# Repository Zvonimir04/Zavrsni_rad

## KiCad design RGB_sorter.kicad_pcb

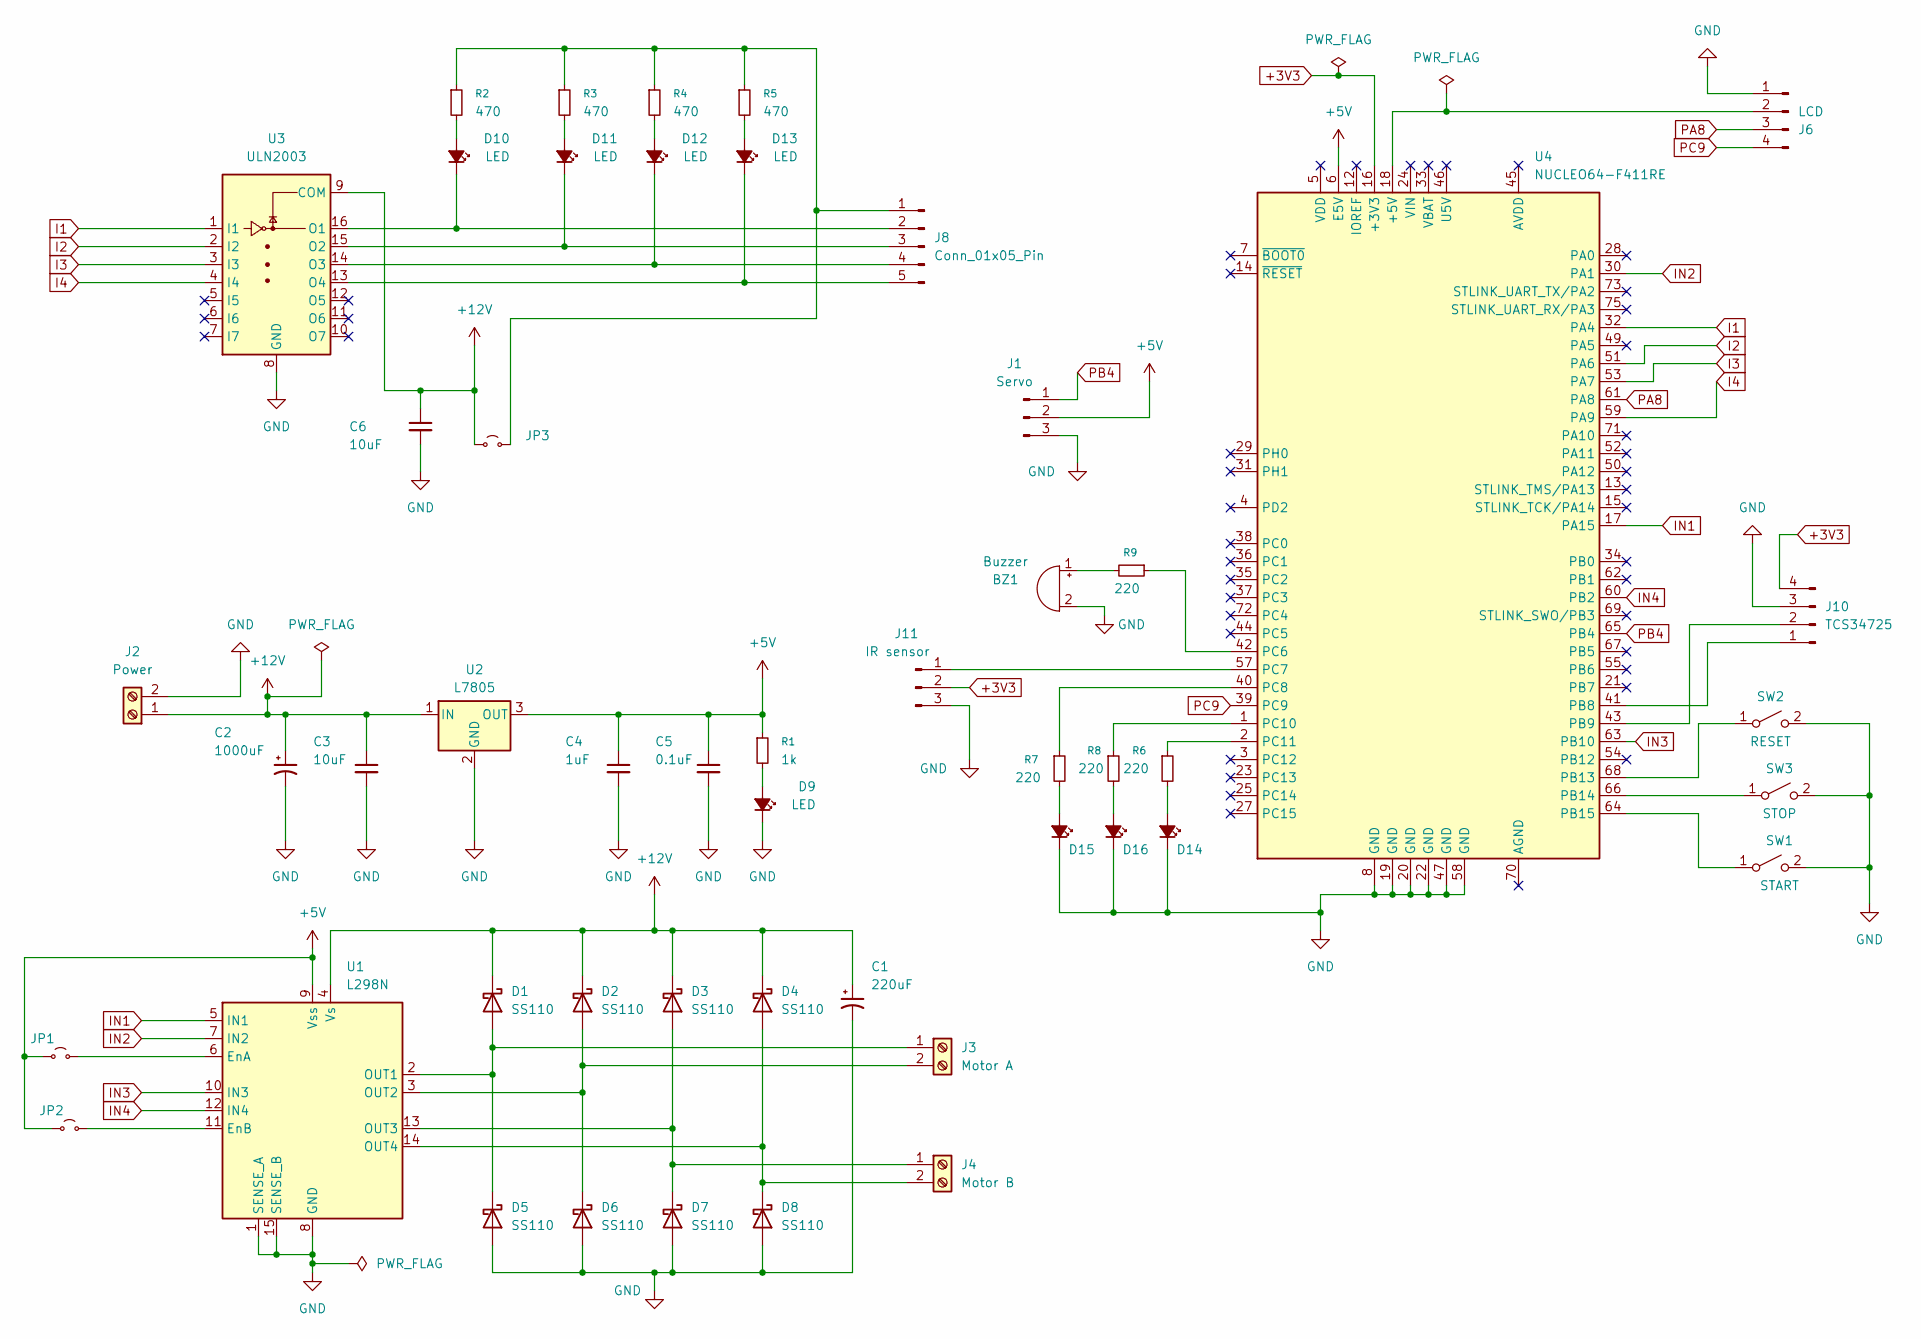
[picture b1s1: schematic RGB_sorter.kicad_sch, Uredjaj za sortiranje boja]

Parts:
BZ1: Buzzer; Buzzer_12x9.5RM7.6
C1: 220uF; CP_Elec_8x10.5
C2: 1000uF; CP_Elec_10x10.5
C3, C6: 10uF; C_1206_3216Metric
C4: 1uF; C_0805_2012Metric
C5: 0.1uF; C_0805_2012Metric
D1, D2, D3, D4, D5, D6, D7, D8: SS110; D_SMA
D9: LED; LED_0805_2012Metric
D10, D11, D12, D13: LED; LED_1206_3216Metric
D14: LED_Red; LED_D5.0mm
D15: LED_Green; LED_D5.0mm
D16: LED_Blue; LED_D5.0mm
J1: Servo; PinHeader_1x03_P2.54mm_Vertical
J2: Power; TerminalBlock_Phoenix_MKDS-1,5-2-5.08_1x02_P5.08mm_Horizont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
J3: Motor A; TerminalBlock_Phoenix_MKDS-1,5-2-5.08_1x02_P5.08mm_Horizont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
J4: Motor B; TerminalBlock_Phoenix_MKDS-1,5-2-5.08_1x02_P5.08mm_Horizont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
J6: LCD; PinHeader_1x04_P2.54mm_Vertical
J8: Conn_01x05_Pin; JST_XH_B5B-XH-A_1x05_P2.50mm_Vertical
J10: TCS34725; PinHeader_1x04_P2.54mm_Vertical
J11: IR sensor; PinHeader_1x03_P2.54mm_Vertical
JP1, JP2, JP3: PinHeader_1x02_P2.54mm_Vertical
R1: 1k; R_0805_2012Metric
R2, R3, R4, R5: 470; R_0805_2012Metric
R6, R7, R8, R9: 220; R_0805_2012Metric
SW1: START; SW_PUSH-12mm_Wuerth-430476085716
SW2: RESET; SW_PUSH-12mm_Wuerth-430476085716
SW3: STOP; SW_PUSH-12mm_Wuerth-430476085716
U1: L298N; L298n
U2: L7805; TO-252-2
U3: ULN2003; SOIC-16_3.9x9.9mm_P1.27mm
U4: NUCLEO64-F411RE; MODULE_NUCLEO-F446RE

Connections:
+3V3: J10.4, J11.2, U4.16 (+3V3)
+5V: C4.1, C5.1, J1.2, JP1.1 (A), JP2.1 (A), R1.1, U1.9 (Vss), U2.3 (OUT), U4.6 (E5V)
+12V: C1.1, C2.1, C3.1, C6.1, D1.1 (K), D2.1 (K), D3.1 (K), D4.1 (K), J2.1, JP3.1 (A), U1.4 (Vs), U2.1 (IN), U3.9 (COM)
GND: BZ1.2 (-), C1.2, C2.2, C3.2, C4.2, C5.2, C6.2, D5.2 (A), D6.2 (A), D7.2 (A), D8.2 (A), D9.1 (K), D14.1 (K), D15.1 (K), D16.1 (K), J1.3, J2.2, J6.1, J10.3, J11.3, SW1.2 (B), SW2.2 (B), SW3.2 (B), U1.1 (SENSE_A), U1.8 (GND), U1.15 (SENSE_B), U2.2 (GND), U3.8 (GND), U4.8 (GND), U4.19 (GND), U4.20 (GND), U4.22 (GND), U4.47 (GND), U4.58 (GND)
I1: U3.1 (I1), U4.32 (PA4)
I2: U3.2 (I2), U4.51 (PA6)
I3: U3.3 (I3), U4.53 (PA7)
I4: U3.4 (I4), U4.59 (PA9)
IN1: U1.5 (IN1), U4.17 (PA15)
IN2: U1.7 (IN2), U4.30 (PA1)
IN3: U1.10 (IN3), U4.63 (PB10)
IN4: U1.12 (IN4), U4.60 (PB2)
unnamed: BZ1.1 (+), R9.2
unnamed: D1.2 (A), D5.1 (K), J3.1, U1.2 (OUT1)
unnamed: D2.2 (A), D6.1 (K), J3.2, U1.3 (OUT2)
unnamed: D3.2 (A), D7.1 (K), J4.1, U1.13 (OUT3)
unnamed: D4.2 (A), D8.1 (K), J4.2, U1.14 (OUT4)
unnamed: D9.2 (A), R1.2
unnamed: D10.2 (A), R2.2
unnamed: D10.1 (K), J8.2, U3.16 (O1)
unnamed: D11.2 (A), R3.2
unnamed: D11.1 (K), J8.3, U3.15 (O2)
unnamed: D12.2 (A), R4.2
unnamed: D12.1 (K), J8.4, U3.14 (O3)
unnamed: D13.2 (A), R5.2
unnamed: D13.1 (K), J8.5, U3.13 (O4)
unnamed: D14.2 (A), R6.2
unnamed: D15.2 (A), R7.2
unnamed: D16.2 (A), R8.2
unnamed: J6.2, U4.18 (+5V)
unnamed: J8.1, JP3.2 (B), R2.1, R3.1, R4.1, R5.1
unnamed: J10.1, U4.41 (PB8)
unnamed: J10.2, U4.43 (PB9)
unnamed: J11.1, U4.57 (PC7)
unnamed: JP1.2 (B), U1.6 (EnA)
unnamed: JP2.2 (B), U1.11 (EnB)
unnamed: SW1.1 (A), U4.64 (PB15)
unnamed: SW2.1 (A), U4.68 (PB13)
unnamed: SW3.1 (A), U4.66 (PB14)
unnamed: R9.1, U4.42 (PC6)
unnamed: R7.1, U4.40 (PC8)
unnamed: R8.1, U4.1 (PC10)
unnamed: R6.1, U4.2 (PC11)
PA8: J6.3, U4.61 (PA8)
PB4: J1.1, U4.65 (PB4)
PC9: J6.4, U4.39 (PC9)

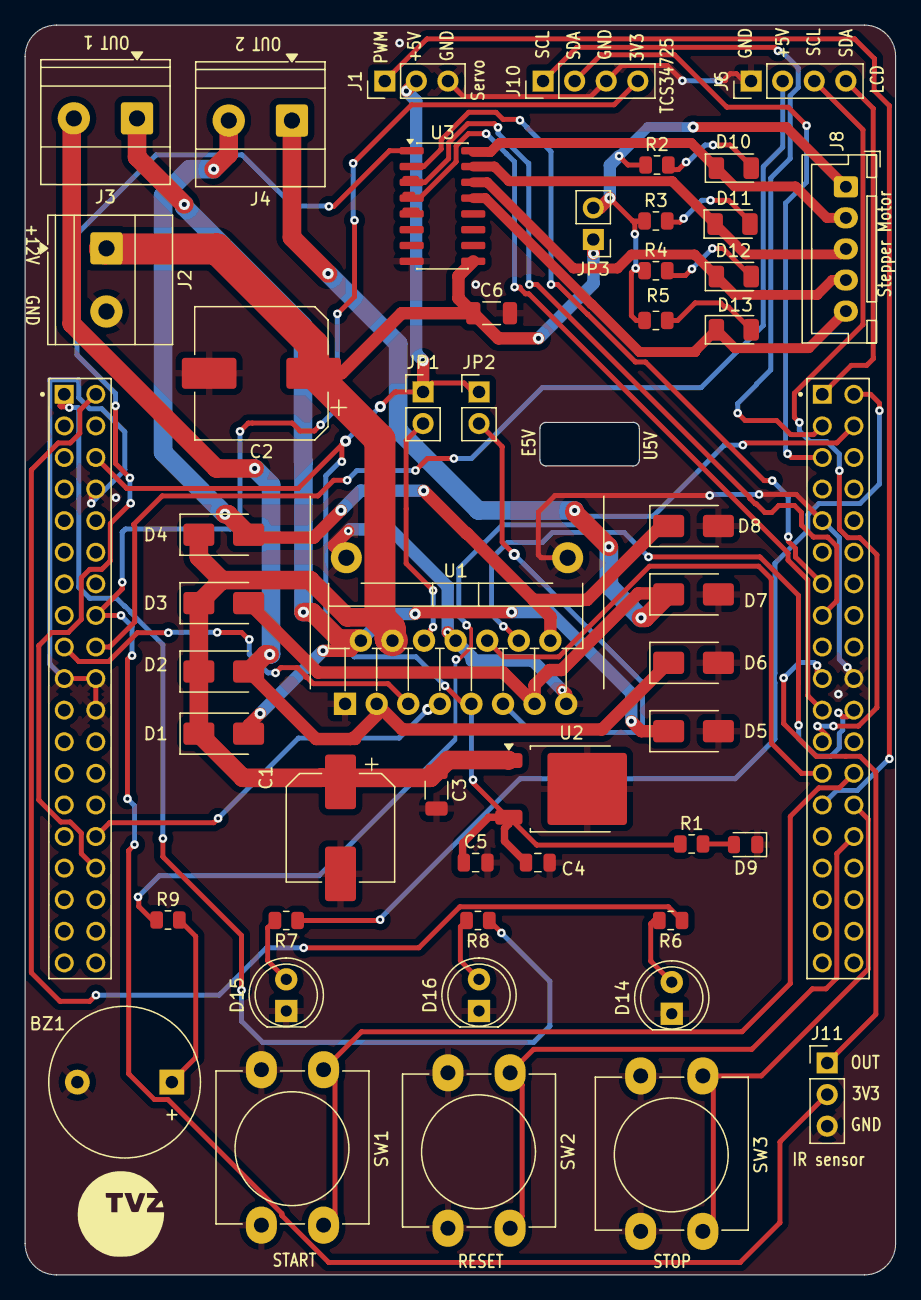
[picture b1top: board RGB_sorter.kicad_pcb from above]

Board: 4 copper layers, 69.9 x 100.4 mm, 50 parts (0 on the bottom side), 46 nets.

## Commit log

2026-04-26 l298n
    motorni drajver
2026-05-12 PCB Uredjaj za sortiranje boja
    PCB edit
2026-05-17 Upgrade PCB-a
    Shematic i PCB edit
